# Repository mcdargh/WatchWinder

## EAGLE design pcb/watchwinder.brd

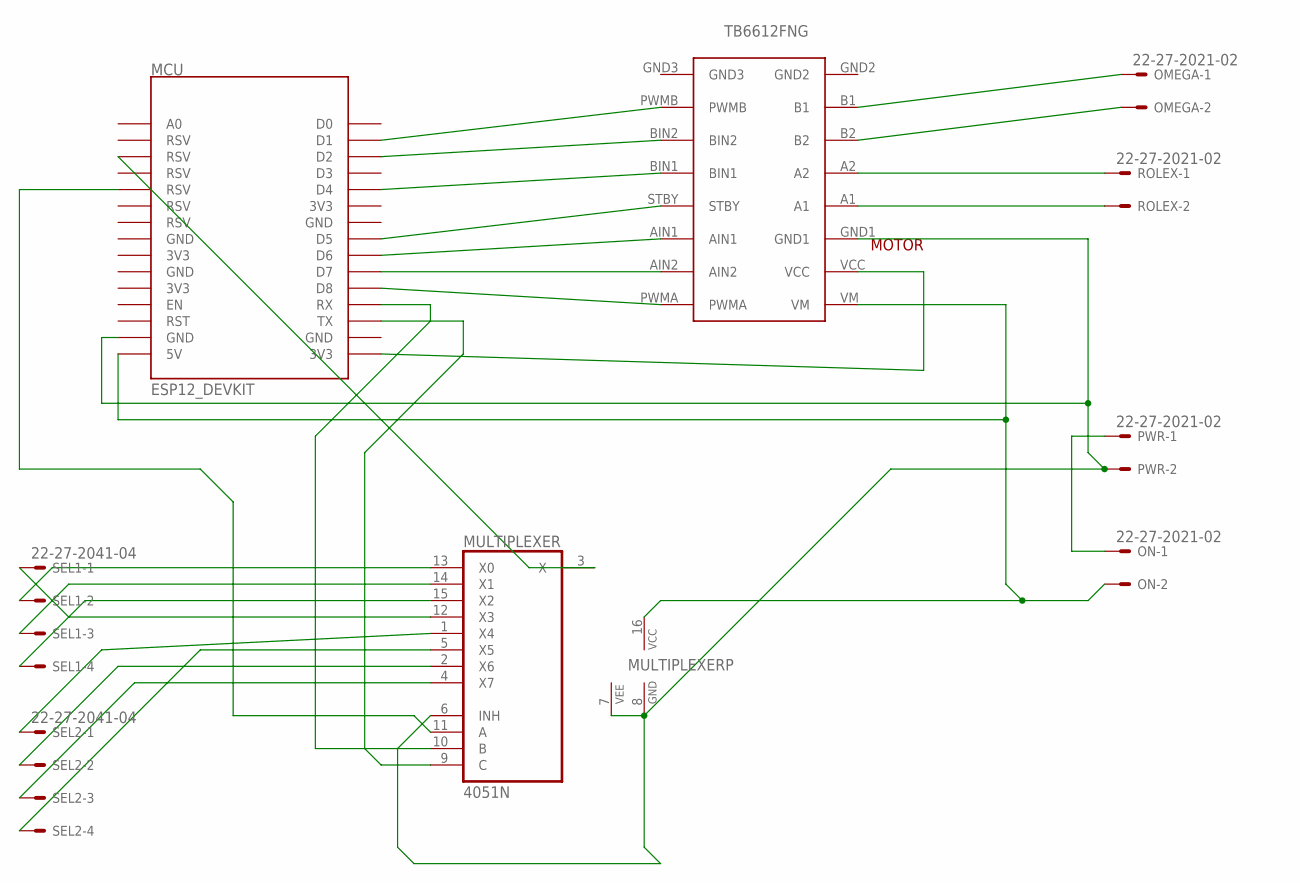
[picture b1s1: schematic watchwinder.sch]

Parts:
MCU: ESP12_DEVKIT
MOTOR: TB6612FNG
MULTIPLEXER: 4051N; DIL16
OMEGA: 22-27-2021-02; 6410-02
ON: 22-27-2021-02; 6410-02
PWR: 22-27-2021-02; 6410-02
ROLEX: 22-27-2021-02; 6410-02
SEL1, SEL2: 22-27-2041-04; 6410-04

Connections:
GND: MCU.GND@1 (GND), MOTOR.GND1, MULTIPLEXER.6 (INH), MULTIPLEXER.7 (VEE), MULTIPLEXER.8 (GND), PWR.2
unnamed: MCU.D1, MOTOR.PWMB
unnamed: MCU.D2, MOTOR.BIN2
unnamed: MCU.D4, MOTOR.BIN1
unnamed: MCU.D5, MOTOR.STBY
unnamed: MCU.D6, MOTOR.AIN1
unnamed: MCU.D7, MOTOR.AIN2
unnamed: MCU.D8, MOTOR.PWMA
unnamed: MOTOR.A2, ROLEX.1
unnamed: MOTOR.A1, ROLEX.2
unnamed: MOTOR.B1, OMEGA.1
unnamed: MOTOR.B2, OMEGA.2
unnamed: MCU.3V3@2 (3V3), MOTOR.VCC
unnamed: ON.1, PWR.1
unnamed: MCU.5V, MOTOR.VM, MULTIPLEXER.16 (VCC), ON.2
unnamed: MULTIPLEXER.12 (X3), SEL1.1
unnamed: MULTIPLEXER.14 (X1), SEL1.3
unnamed: MULTIPLEXER.15 (X2), SEL1.4
unnamed: MULTIPLEXER.13 (X0), SEL1.2
unnamed: MULTIPLEXER.1 (X4), SEL2.1
unnamed: MULTIPLEXER.2 (X6), SEL2.2
unnamed: MULTIPLEXER.4 (X7), SEL2.3
unnamed: MULTIPLEXER.5 (X5), SEL2.4
unnamed: MCU.RX, MULTIPLEXER.10 (B)
unnamed: MCU.RSV@3 (RSV), MULTIPLEXER.11 (A)
unnamed: MCU.TX, MULTIPLEXER.9 (C)
unnamed: MCU.RSV@1 (RSV), MULTIPLEXER.3 (X)

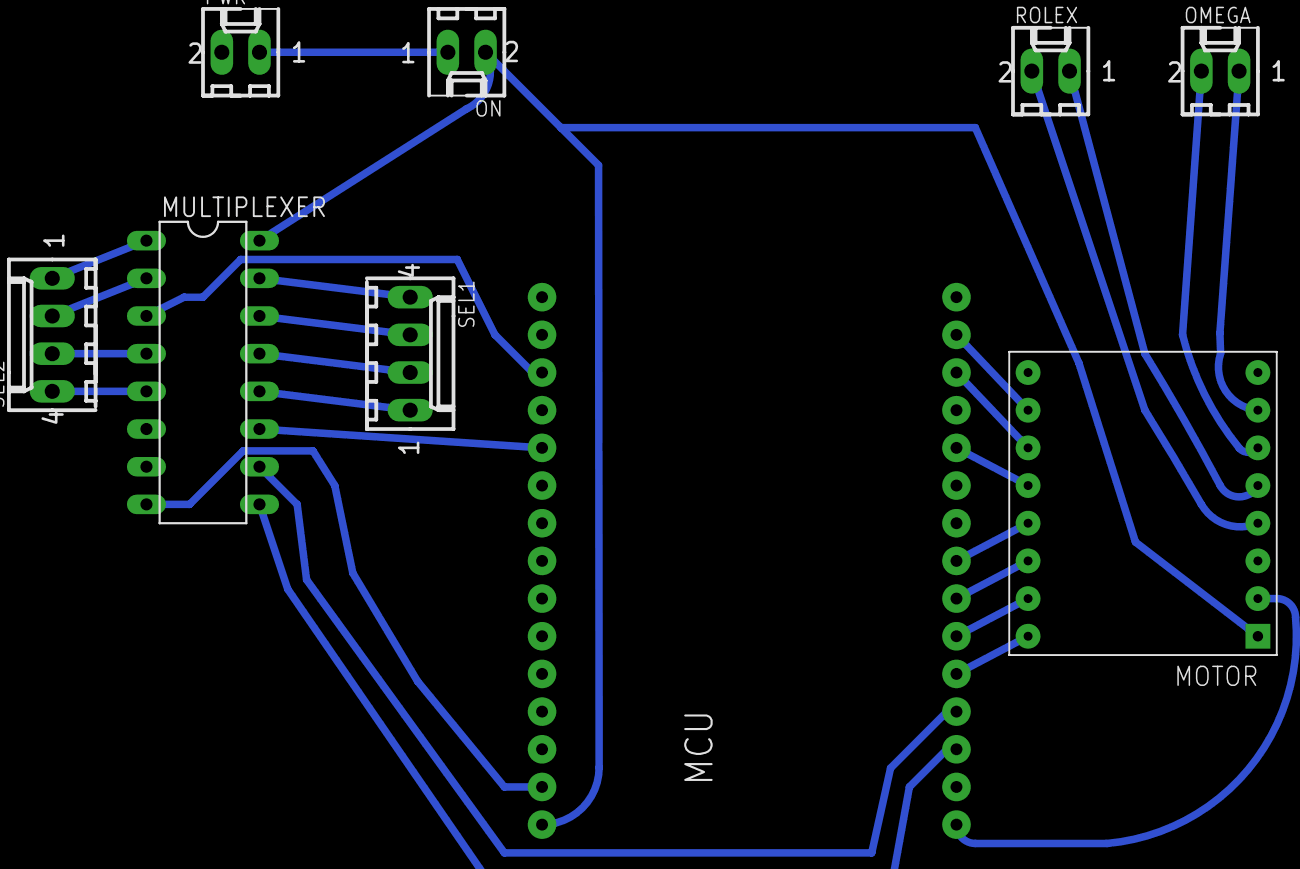
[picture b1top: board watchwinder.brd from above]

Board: 2 copper layers, 9 parts (0 on the bottom side), 27 nets.

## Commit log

2017-05-10 Ignore local settings file (passwords and all that)
2017-05-10 Add pcb
2017-05-11 updated pins based on pcb design
2017-05-11 update pcb for one layer
2017-05-11 Add in sketch for pcb updates
2017-05-31 Added in multiplexer to pcb
2017-06-07 Changed to Eagle CAD
2017-06-07 Compacted a bit
2017-07-03 Worked to one layer only
2017-07-04 Prepped for cnc
2017-07-06 Printed board
2017-07-06 update for vscode
2017-07-06 Updated messages and timeouts
2017-07-06 Implemented OTA update
2017-07-06 don't try to send to dweet if no wifi
2017-07-07 Changed wifi connect timeout and make log safe for dweet
2017-07-12 fixed timing issue and added log method to send to dweet or io
